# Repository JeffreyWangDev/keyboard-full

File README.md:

# A full keyboard bassed on my [numpad](https://github.com/JeffreyWangDev/keyboard-numpad)

This is a 96% keyboard with no leds atm but will be added soon! 
[Video](https://cloud-jp32pzjfd-hack-club-bot.vercel.app/0img_1993.mp4) This is the numpad but the keyboard is just bigger and with a diff controller.

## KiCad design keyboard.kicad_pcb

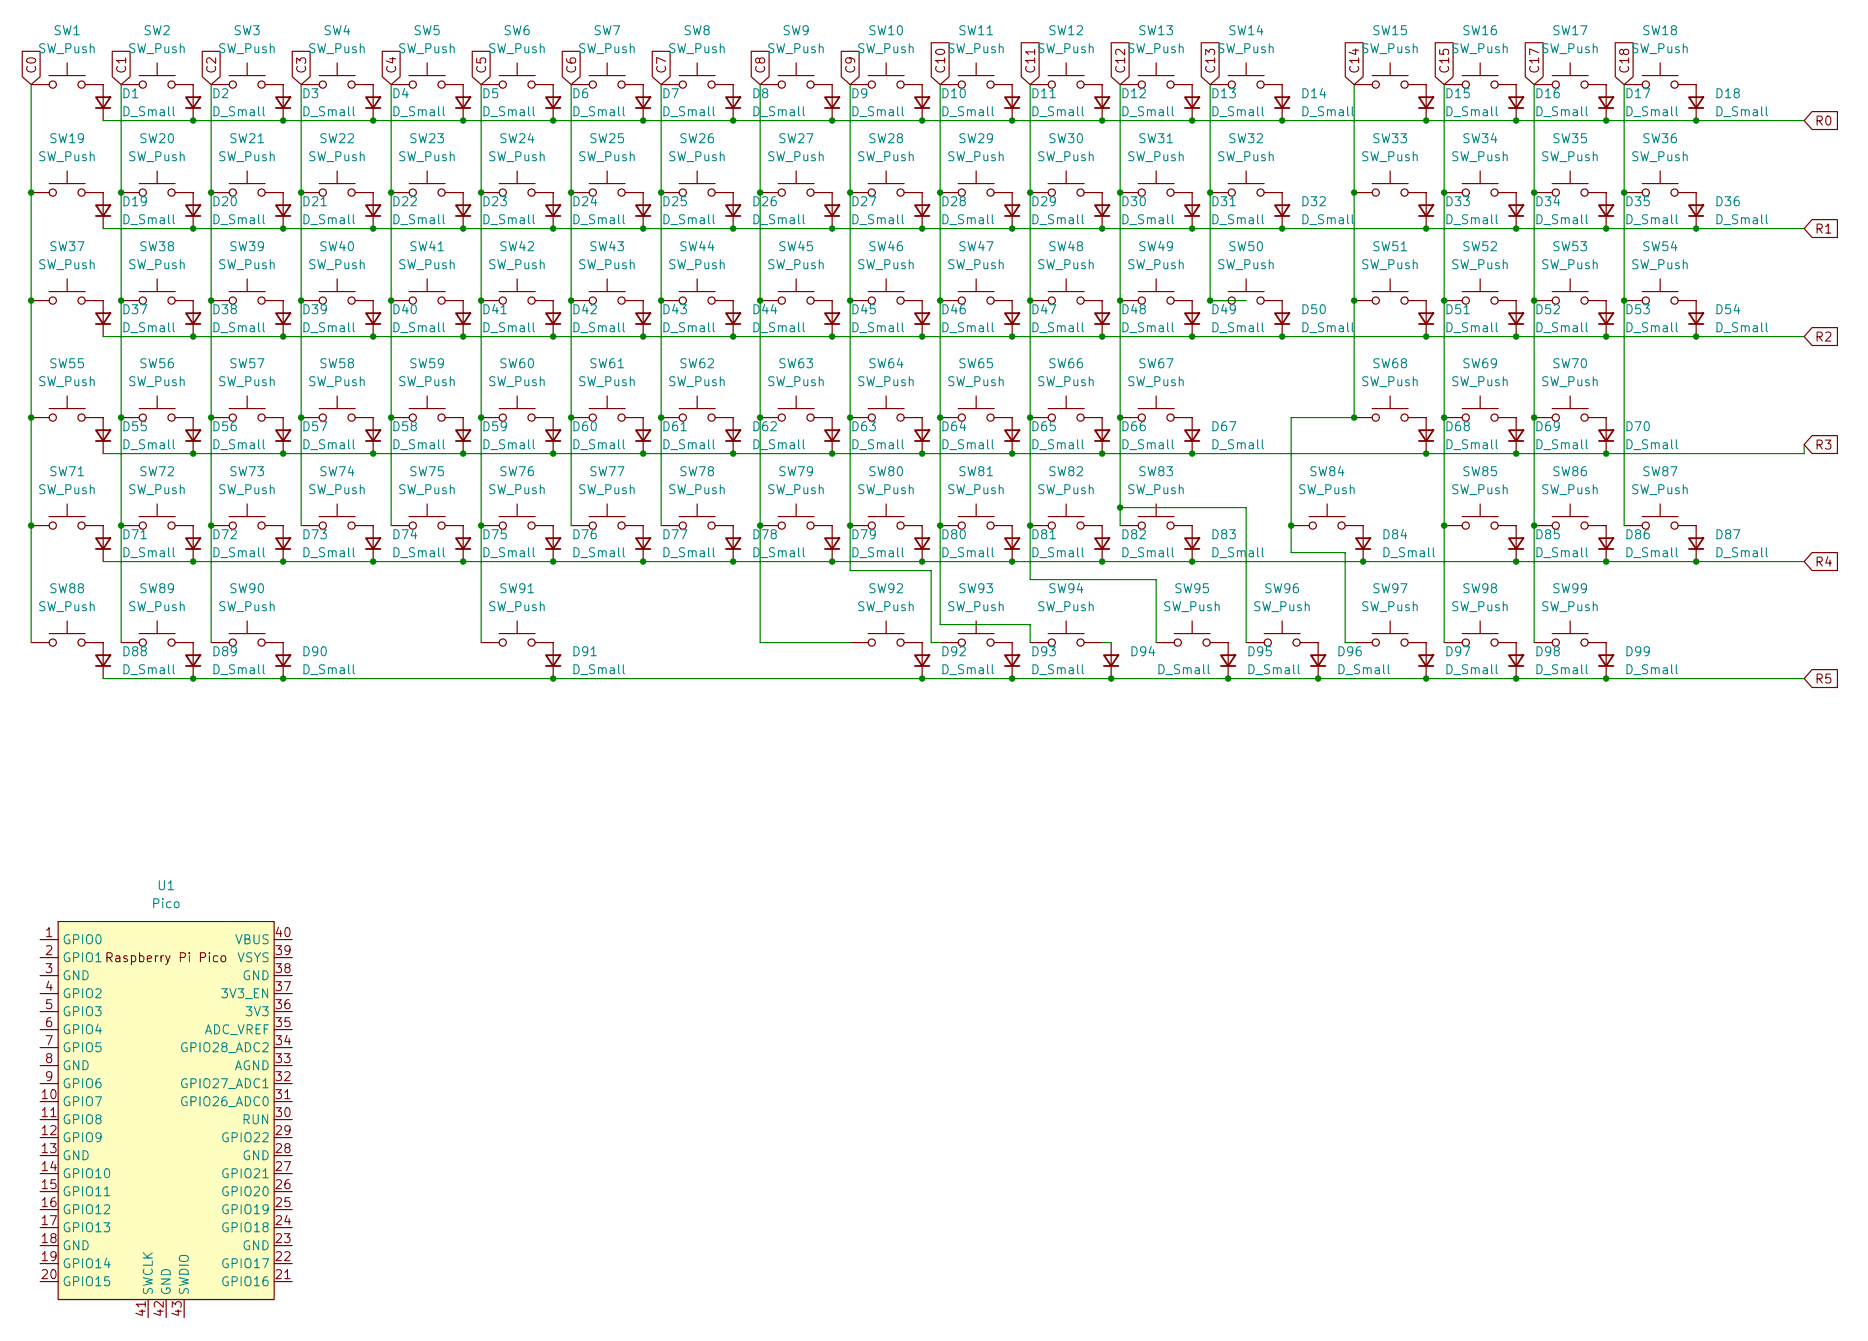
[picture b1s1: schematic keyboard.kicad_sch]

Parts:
D1, D2, D3, D4, D5, D6, D7, D8, D9, D10, D11, D12, D13, D14, D15, D16, D17, D18, D19, D20, D21, D22, D23, D24, D25, D26, D27, D28, D29, D30, D31, D32, D33, D34, D35, D36, D37, D38, D39, D40, D41, D42, D43, D44, D45, D46, D47, D48, D49, D50, D51, D52, D53, D54, D55, D56, D57, D58, D59, D60, D61, D62, D63, D64, D65, D66, D67, D68, D69, D70, D71, D72, D73, D74, D75, D76, D77, D78, D79, D80, D81, D82, D83, D84, D85, D86, D87, D88, D89, D90, D91, D92, D93, D94, D95, D96, D97, D98, D99: D_Small; D_SOD-123; LCSC C64898
SW1, SW2, SW3, SW4, SW5, SW6, SW7, SW8, SW9, SW10, SW11, SW12, SW13, SW14, SW15, SW16, SW17, SW18, SW19, SW20, SW21, SW22, SW23, SW24, SW25, SW26, SW27, SW28, SW29, SW30, SW31, SW32, SW33, SW34, SW35, SW36, SW38, SW39, SW40, SW41, SW42, SW43, SW44, SW45, SW46, SW47, SW48, SW49, SW51, SW52, SW53, SW54, SW56, SW57, SW58, SW59, SW60, SW61, SW62, SW63, SW64, SW65, SW66, SW67, SW68, SW69, SW70, SW71, SW72, SW73, SW74, SW75, SW76, SW77, SW78, SW79, SW80, SW81, SW83, SW84, SW85, SW86, SW87, SW91, SW92, SW93, SW94, SW95, SW96, SW97, SW98, SW99: SW_Push; SW_MX_HS_CPG151101S11_1u
SW37, SW50: SW_Push; SW_MX_HS_CPG151101S11_1.5u
SW55, SW82: SW_Push; SW_MX_HS_CPG151101S11_1.75u
SW88, SW89, SW90: SW_Push; SW_MX_HS_CPG151101S11_1.25u
U1: Pico; RPi_Pico_SMD_TH

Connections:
C0: SW1.1, SW19.1, SW37.1, SW55.1, SW71.1, SW88.1
C1: SW2.1, SW20.1, SW38.1, SW56.1, SW72.1, SW89.1
C2: SW3.1, SW21.1, SW39.1, SW57.1, SW73.1, SW90.1
C3: SW4.1, SW22.1, SW40.1, SW58.1, SW74.1
C4: SW5.1, SW23.1, SW41.1, SW59.1, SW75.1
C5: SW6.1, SW24.1, SW42.1, SW60.1, SW76.1, SW91.1
C6: SW7.1, SW25.1, SW43.1, SW61.1, SW77.1
C7: SW8.1, SW26.1, SW44.1, SW62.1, SW78.1
C8: SW9.1, SW27.1, SW45.1, SW63.1, SW79.1, SW92.1
C9: SW10.1, SW28.1, SW46.1, SW64.1, SW80.1, SW93.1
C10: SW11.1, SW29.1, SW47.1, SW65.1, SW81.1, SW94.1
C11: SW12.1, SW30.1, SW48.1, SW66.1, SW82.1, SW95.1
C12: SW13.1, SW31.1, SW49.1, SW67.1, SW83.1, SW96.1
C13: SW14.1, SW32.1, SW50.1
C14: SW15.1, SW33.1, SW51.1, SW68.1, SW84.1, SW97.1
C15: SW16.1, SW34.1, SW52.1, SW69.1, SW85.1, SW98.1
C17: SW17.1, SW35.1, SW53.1, SW70.1, SW86.1, SW99.1
C18: SW18.1, SW36.1, SW54.1, SW87.1
unnamed: D1.2 (A), SW1.2
unnamed: D2.2 (A), SW2.2
unnamed: D3.2 (A), SW3.2
unnamed: D4.2 (A), SW4.2
unnamed: D5.2 (A), SW5.2
unnamed: D6.2 (A), SW6.2
unnamed: D7.2 (A), SW7.2
unnamed: D8.2 (A), SW8.2
unnamed: D9.2 (A), SW9.2
unnamed: D10.2 (A), SW10.2
unnamed: D11.2 (A), SW11.2
unnamed: D12.2 (A), SW12.2
unnamed: D13.2 (A), SW13.2
unnamed: D14.2 (A), SW14.2
unnamed: D15.2 (A), SW15.2
unnamed: D16.2 (A), SW16.2
unnamed: D17.2 (A), SW17.2
unnamed: D18.2 (A), SW18.2
unnamed: D19.2 (A), SW19.2
unnamed: D20.2 (A), SW20.2
unnamed: D21.2 (A), SW21.2
unnamed: D22.2 (A), SW22.2
unnamed: D23.2 (A), SW23.2
unnamed: D24.2 (A), SW24.2
unnamed: D25.2 (A), SW25.2
unnamed: D26.2 (A), SW26.2
unnamed: D27.2 (A), SW27.2
unnamed: D28.2 (A), SW28.2
unnamed: D29.2 (A), SW29.2
unnamed: D30.2 (A), SW30.2
unnamed: D31.2 (A), SW31.2
unnamed: D32.2 (A), SW32.2
unnamed: D33.2 (A), SW33.2
unnamed: D34.2 (A), SW34.2
unnamed: D35.2 (A), SW35.2
unnamed: D36.2 (A), SW36.2
unnamed: D37.2 (A), SW37.2
unnamed: D38.2 (A), SW38.2
unnamed: D39.2 (A), SW39.2
unnamed: D40.2 (A), SW40.2
unnamed: D41.2 (A), SW41.2
unnamed: D42.2 (A), SW42.2
unnamed: D43.2 (A), SW43.2
unnamed: D44.2 (A), SW44.2
unnamed: D45.2 (A), SW45.2
unnamed: D46.2 (A), SW46.2
unnamed: D47.2 (A), SW47.2
unnamed: D48.2 (A), SW48.2
unnamed: D49.2 (A), SW49.2
unnamed: D50.2 (A), SW50.2
unnamed: D51.2 (A), SW51.2
unnamed: D52.2 (A), SW52.2
unnamed: D53.2 (A), SW53.2
unnamed: D54.2 (A), SW54.2
unnamed: D55.2 (A), SW55.2
unnamed: D56.2 (A), SW56.2
unnamed: D57.2 (A), SW57.2
unnamed: D58.2 (A), SW58.2
unnamed: D59.2 (A), SW59.2
unnamed: D60.2 (A), SW60.2
unnamed: D61.2 (A), SW61.2
unnamed: D62.2 (A), SW62.2
unnamed: D63.2 (A), SW63.2
unnamed: D64.2 (A), SW64.2
unnamed: D65.2 (A), SW65.2
unnamed: D66.2 (A), SW66.2
unnamed: D67.2 (A), SW67.2
unnamed: D68.2 (A), SW68.2
unnamed: D69.2 (A), SW69.2
unnamed: D70.2 (A), SW70.2
unnamed: D71.2 (A), SW71.2
unnamed: D72.2 (A), SW72.2
unnamed: D73.2 (A), SW73.2
unnamed: D74.2 (A), SW74.2
unnamed: D75.2 (A), SW75.2
unnamed: D76.2 (A), SW76.2
unnamed: D77.2 (A), SW77.2
unnamed: D78.2 (A), SW78.2
unnamed: D79.2 (A), SW79.2
unnamed: D80.2 (A), SW80.2
unnamed: D81.2 (A), SW81.2
unnamed: D82.2 (A), SW82.2
unnamed: D83.2 (A), SW83.2
unnamed: D84.2 (A), SW84.2
unnamed: D85.2 (A), SW85.2
unnamed: D86.2 (A), SW86.2
unnamed: D87.2 (A), SW87.2
unnamed: D88.2 (A), SW88.2
unnamed: D89.2 (A), SW89.2
unnamed: D90.2 (A), SW90.2
unnamed: D91.2 (A), SW91.2
unnamed: D92.2 (A), SW92.2
unnamed: D93.2 (A), SW93.2
unnamed: D94.2 (A), SW94.2
unnamed: D95.2 (A), SW95.2
unnamed: D96.2 (A), SW96.2
unnamed: D97.2 (A), SW97.2
unnamed: D98.2 (A), SW98.2
unnamed: D99.2 (A), SW99.2
R0: D1.1 (K), D2.1 (K), D3.1 (K), D4.1 (K), D5.1 (K), D6.1 (K), D7.1 (K), D8.1 (K), D9.1 (K), D10.1 (K), D11.1 (K), D12.1 (K), D13.1 (K), D14.1 (K), D15.1 (K), D16.1 (K), D17.1 (K), D18.1 (K)
R1: D19.1 (K), D20.1 (K), D21.1 (K), D22.1 (K), D23.1 (K), D24.1 (K), D25.1 (K), D26.1 (K), D27.1 (K), D28.1 (K), D29.1 (K), D30.1 (K), D31.1 (K), D32.1 (K), D33.1 (K), D34.1 (K), D35.1 (K), D36.1 (K)
R2: D37.1 (K), D38.1 (K), D39.1 (K), D40.1 (K), D41.1 (K), D42.1 (K), D43.1 (K), D44.1 (K), D45.1 (K), D46.1 (K), D47.1 (K), D48.1 (K), D49.1 (K), D50.1 (K), D51.1 (K), D52.1 (K), D53.1 (K), D54.1 (K)
R3: D55.1 (K), D56.1 (K), D57.1 (K), D58.1 (K), D59.1 (K), D60.1 (K), D61.1 (K), D62.1 (K), D63.1 (K), D64.1 (K), D65.1 (K), D66.1 (K), D67.1 (K), D68.1 (K), D69.1 (K), D70.1 (K)
R4: D71.1 (K), D72.1 (K), D73.1 (K), D74.1 (K), D75.1 (K), D76.1 (K), D77.1 (K), D78.1 (K), D79.1 (K), D80.1 (K), D81.1 (K), D82.1 (K), D83.1 (K), D84.1 (K), D85.1 (K), D86.1 (K), D87.1 (K)
R5: D88.1 (K), D89.1 (K), D90.1 (K), D91.1 (K), D92.1 (K), D93.1 (K), D94.1 (K), D95.1 (K), D96.1 (K), D97.1 (K), D98.1 (K), D99.1 (K)

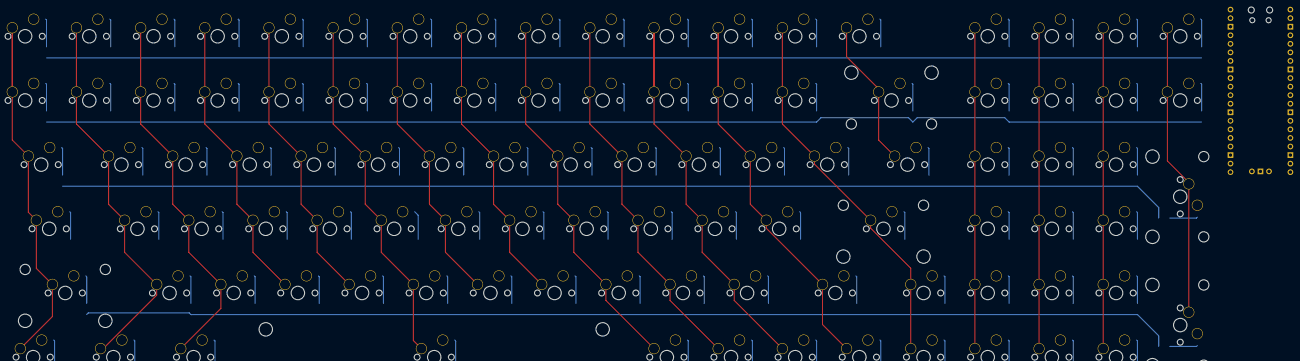
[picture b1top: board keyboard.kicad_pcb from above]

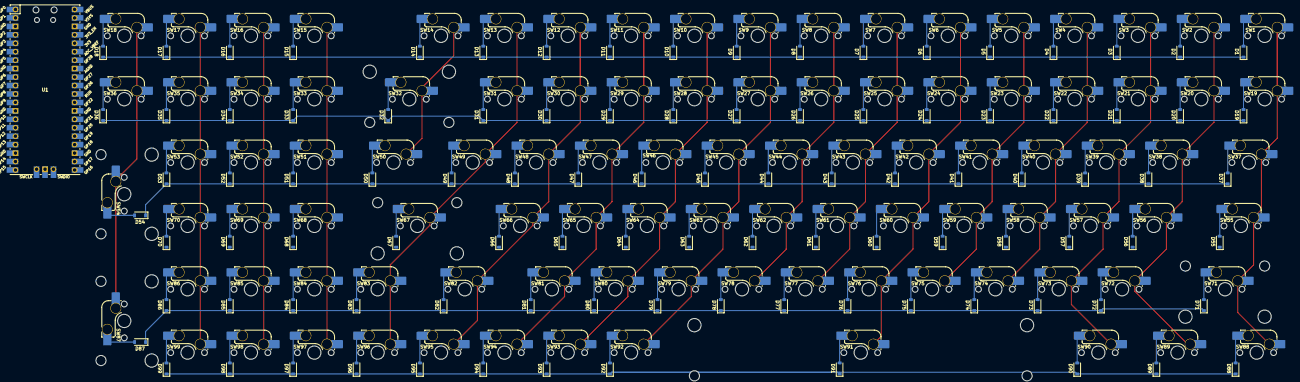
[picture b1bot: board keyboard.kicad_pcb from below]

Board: 2 copper layers, 199 parts (199 on the bottom side), 123 nets.

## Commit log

2025-02-01 init
